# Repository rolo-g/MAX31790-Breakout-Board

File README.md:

# MAX31790-Breakout-Board

The schematic and PCB can be viewed without installing KiCad 8.0 by using [KiCanvas, an online KiCad viewer](https://github.com/theacodes/kicanvas)

https://kicanvas.org/?github=https%3A%2F%2Fgithub.com%2Frolo-g%2FMAX31790-Breakout-Board

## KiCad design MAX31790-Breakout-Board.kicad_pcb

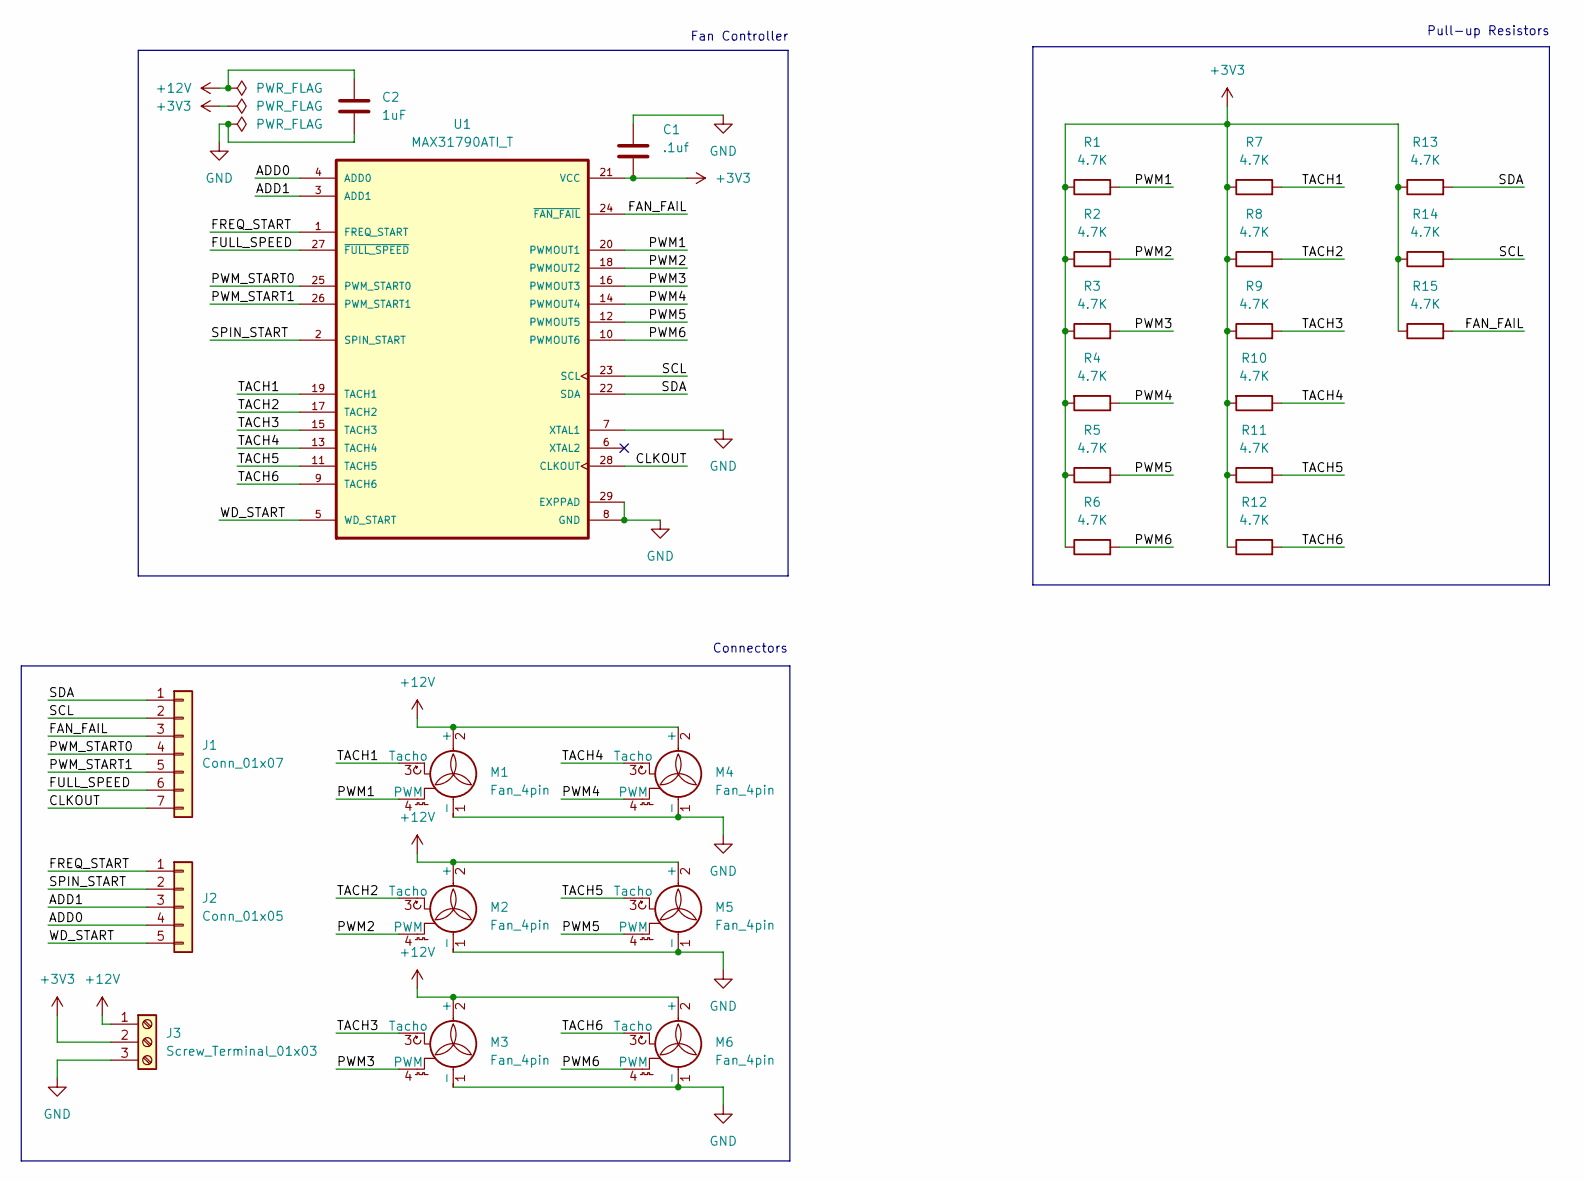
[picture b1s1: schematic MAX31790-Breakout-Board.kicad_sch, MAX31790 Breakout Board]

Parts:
C1: .1uf; C_0603_1608Metric
C2: 1uF; C_0603_1608Metric
J1: Conn_01x07; PinHeader_1x07_P2.54mm_Vertical
J2: Conn_01x05; PinHeader_1x05_P2.54mm_Vertical
J3: Screw_Terminal_01x03; TerminalBlock_Phoenix_MPT-0,5-3-2.54_1x03_P2.54mm_Horizontal
M1, M2, M3, M4, M5, M6: Fan_4pin; FanPinHeader_1x04_P2.54mm_Vertical
R1, R2, R3, R4, R5, R6, R7, R8, R9, R10, R11, R12, R13, R14, R15: 4.7K; R_0603_1608Metric
U1: MAX31790ATI_T; QFN40P400X400X80-29N260X260; PART_REV 2

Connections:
+3V3: C1.2, J3.2, R1.1, R2.1, R3.1, R4.2, R5.1, R6.1, R7.1, R8.1, R9.1, R10.2, R11.1, R12.1, R13.1, R14.1, R15.1, U1.21 (VCC)
+12V: C2.1, J3.1, M1.2 (+), M2.2 (+), M3.2 (+), M4.2 (+), M5.2 (+), M6.2 (+)
/ADD0: J2.4, U1.4 (ADD0)
/ADD1: J2.3, U1.3 (ADD1)
/CLKOUT: J1.7, U1.28 (CLKOUT)
/FAN_FAIL: J1.3, R15.2, U1.24 (~FAN_FAIL)
/FREQ_START: J2.1, U1.1 (FREQ_START)
/FULL_SPEED: J1.6, U1.27 (~FULL_SPEED)
/PWM1: M1.4 (PWM), R1.2, U1.20 (PWMOUT1)
/PWM2: M2.4 (PWM), R2.2, U1.18 (PWMOUT2)
/PWM3: M3.4 (PWM), R3.2, U1.16 (PWMOUT3)
/PWM4: M4.4 (PWM), R4.1, U1.14 (PWMOUT4)
/PWM5: M5.4 (PWM), R5.2, U1.12 (PWMOUT5)
/PWM6: M6.4 (PWM), R6.2, U1.10 (PWMOUT6)
/PWM_START0: J1.4, U1.25 (PWM_START0)
/PWM_START1: J1.5, U1.26 (PWM_START1)
/SCL: J1.2, R14.2, U1.23 (SCL)
/SDA: J1.1, R13.2, U1.22 (SDA)
/SPIN_START: J2.2, U1.2 (SPIN_START)
/TACH1: M1.3 (Tacho), R7.2, U1.19 (TACH1)
/TACH2: M2.3 (Tacho), R8.2, U1.17 (TACH2)
/TACH3: M3.3 (Tacho), R9.2, U1.15 (TACH3)
/TACH4: M4.3 (Tacho), R10.1, U1.13 (TACH4)
/TACH5: M5.3 (Tacho), R11.2, U1.11 (TACH5)
/TACH6: M6.3 (Tacho), R12.2, U1.9 (TACH6)
/WD_START: J2.5, U1.5 (WD_START)
GND: C1.1, C2.2, J3.3, M1.1 (-), M2.1 (-), M3.1 (-), M4.1 (-), M5.1 (-), M6.1 (-), U1.7 (XTAL1), U1.8 (GND), U1.29 (EXPPAD)

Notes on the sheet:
Connectors
Pull-up Resistors
Fan Controller

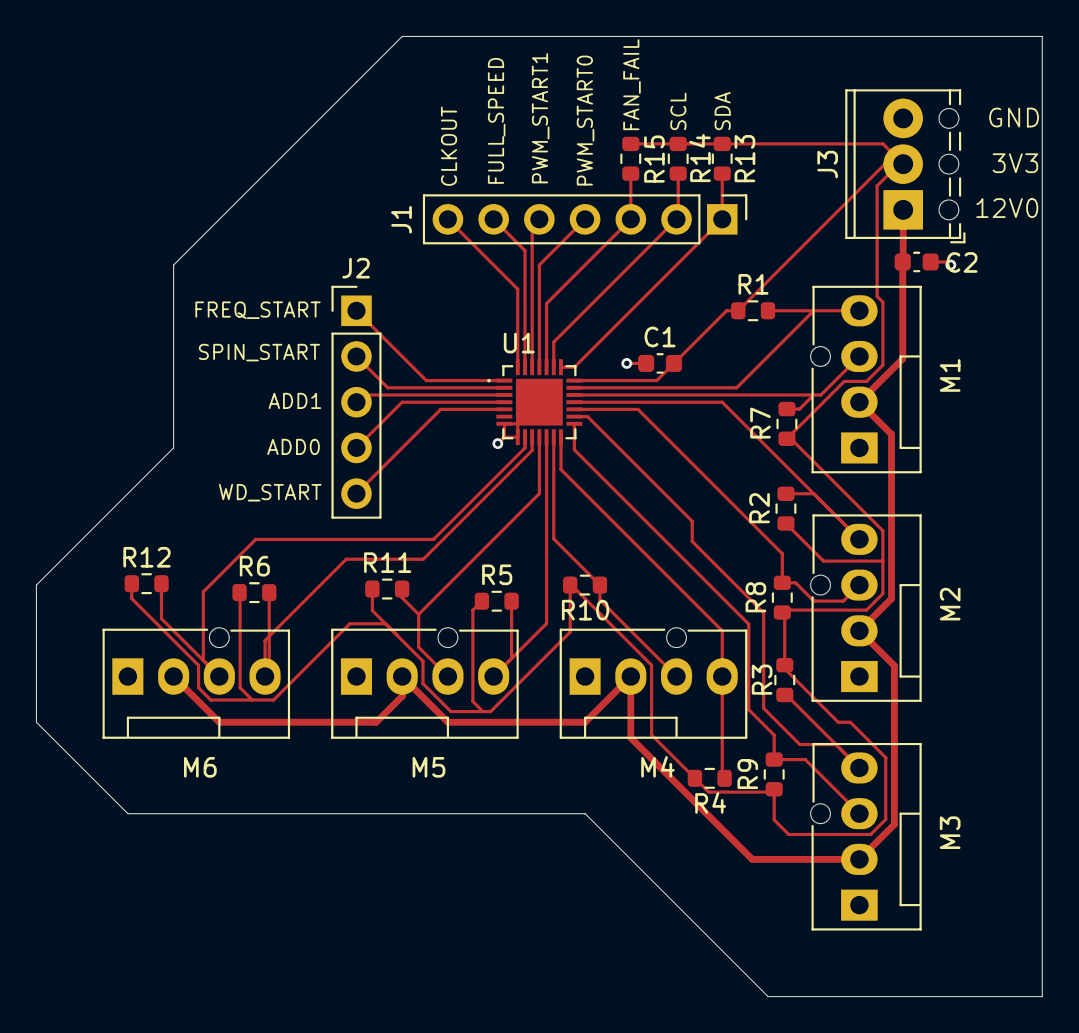
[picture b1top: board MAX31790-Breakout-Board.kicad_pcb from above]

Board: 2 copper layers, 55.9 x 53.3 mm, 27 parts (0 on the bottom side), 27 nets.

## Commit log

2024-06-07 Added +12V line for fan power
2024-06-07 Added page settings
2024-06-07 Added ground plane, increased +12v track width
2024-06-16 Create LICENSE
